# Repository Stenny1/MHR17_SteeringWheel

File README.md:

# MHR17_SteeringWheel

Eagle files for MHybrid's 2017 Steering Wheel PCB

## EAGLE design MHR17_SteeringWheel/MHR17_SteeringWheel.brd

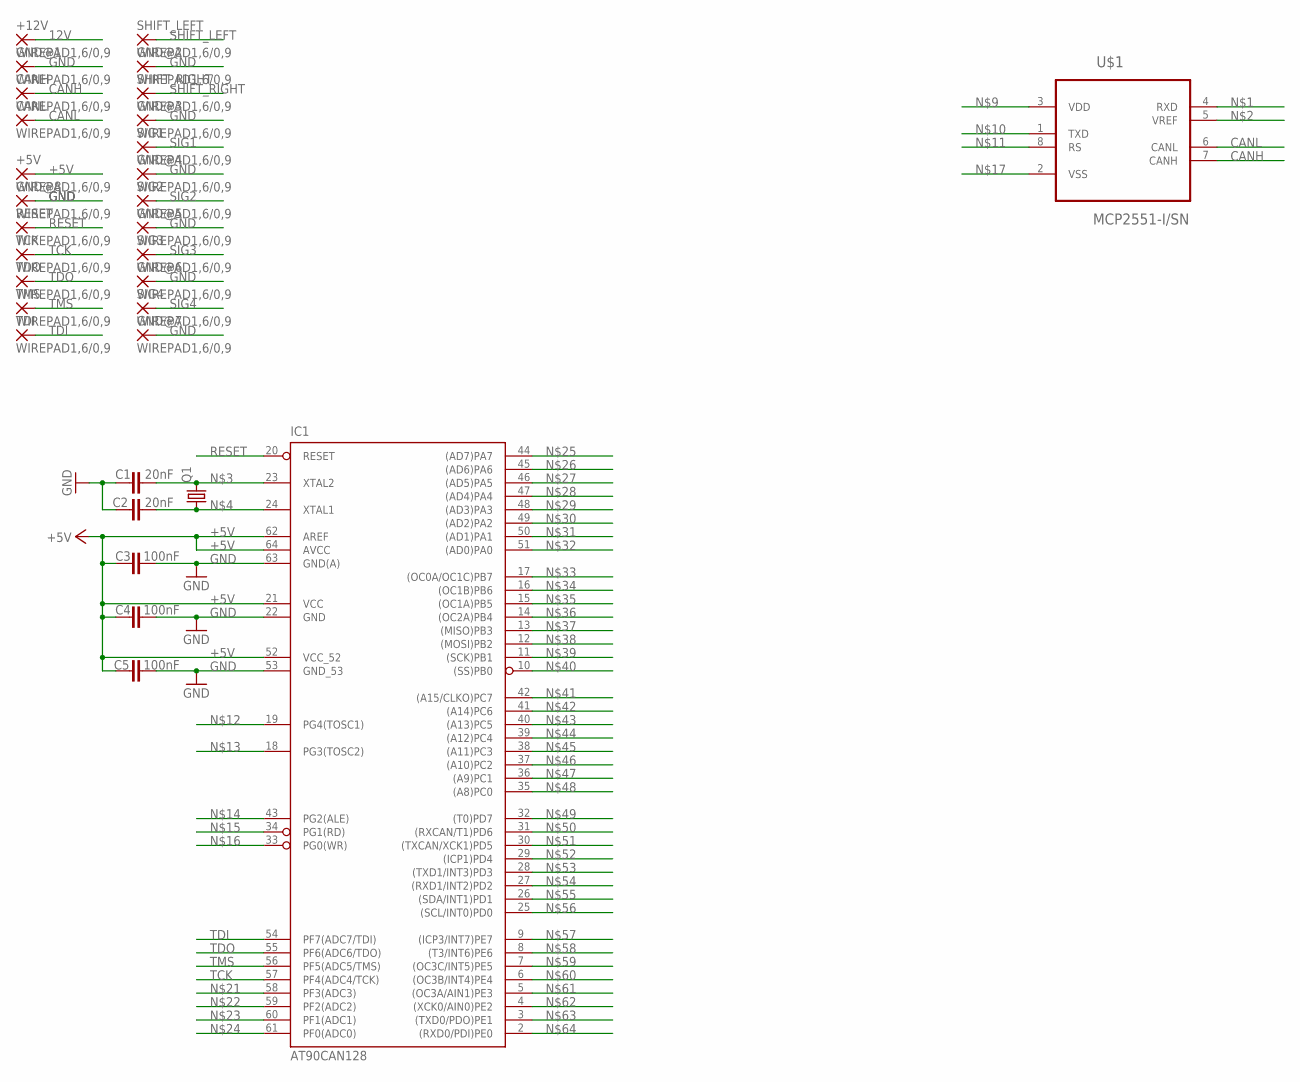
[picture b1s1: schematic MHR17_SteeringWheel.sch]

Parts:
+5V, +12V: WIREPAD1,6/0,9; 1,6/0,9
C1, C2: 20nF; C0603
C3, C4, C5: 100nF; C0603
CANH: WIREPAD1,6/0,9; 1,6/0,9
CANL: WIREPAD1,6/0,9; 1,6/0,9
GND@1, GND@2, GND@3, GND@4, GND@5, GND@6, GND@7, GND@8: WIREPAD1,6/0,9; 1,6/0,9
IC1: AT90CAN128; TQFP64
Q1: CRYSTALHC49S; HC49/S
RESET: WIREPAD1,6/0,9; 1,6/0,9
SHIFT_LEFT: WIREPAD1,6/0,9; 1,6/0,9
SHIFT_RIGHT: WIREPAD1,6/0,9; 1,6/0,9
SIG1, SIG2, SIG3, SIG4: WIREPAD1,6/0,9; 1,6/0,9
TCK: WIREPAD1,6/0,9; 1,6/0,9
TDI: WIREPAD1,6/0,9; 1,6/0,9
TDO: WIREPAD1,6/0,9; 1,6/0,9
TMS: WIREPAD1,6/0,9; 1,6/0,9
U$1: MCP2551-I/SN; SOIC127P600X175-8N

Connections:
12V: +12V.1
+5V: +5V.1, C3.1, C4.1, C5.1, IC1.21 (VCC), IC1.52 (VCC_52), IC1.62 (AREF), IC1.64 (AVCC)
CANH: CANH.1, U$1.7 (CANH)
CANL: CANL.1, U$1.6 (CANL)
GND: C1.1, C2.1, C3.2, C4.2, C5.2, GND@1.1, GND@2.1, GND@3.1, GND@4.1, GND@5.1, GND@6.1, GND@7.1, GND@8.1, IC1.22 (GND), IC1.53 (GND_53), IC1.63 (GND(A))
unnamed: C1.2, IC1.23 (XTAL2), Q1.2
unnamed: C2.2, IC1.24 (XTAL1), Q1.1
RESET: IC1.20 (RESET), RESET.1
SHIFT_LEFT: SHIFT_LEFT.1
SHIFT_RIGHT: SHIFT_RIGHT.1
SIG1: SIG1.1
SIG2: SIG2.1
SIG3: SIG3.1
SIG4: SIG4.1
TCK: IC1.57 (PF4(ADC4/TCK)), TCK.1
TDI: IC1.54 (PF7(ADC7/TDI)), TDI.1
TDO: IC1.55 (PF6(ADC6/TDO)), TDO.1
TMS: IC1.56 (PF5(ADC5/TMS)), TMS.1

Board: 2 copper layers, 31 parts (1 on the bottom side), 11 nets, no tracks yet.

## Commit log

2017-02-22 added eagle files
2017-02-22 add CAN transiever
2017-02-22 added .brd file
2017-02-22 added output ports, still need to check wiresize
2017-02-22 added frame for schematic
2017-02-25 changed dimensions and added power for various ports
